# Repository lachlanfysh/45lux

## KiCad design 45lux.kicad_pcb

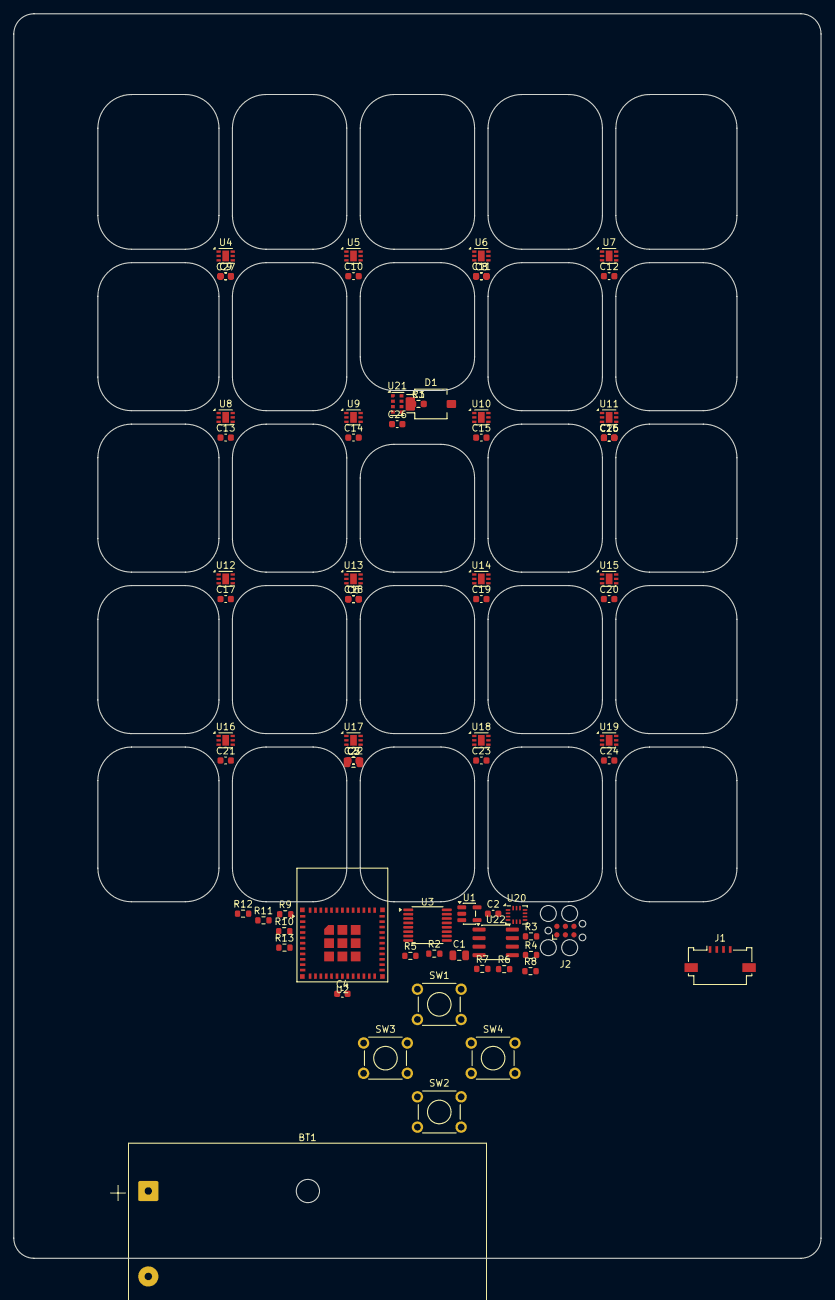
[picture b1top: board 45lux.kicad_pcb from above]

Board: 2 copper layers, 120.0 x 185.0 mm, 70 parts (0 on the bottom side), 23 nets, no tracks yet.

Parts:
BT1: 3xAAA; BatteryHolder_Keystone_2479_3xAAA
C1, C7: 10uF; C_0805_2012Metric
C2, C3, C4, C5, C6, C8, C9, C10, C11, C12, C13, C14, C15, C16, C17, C18, C19, C20, C21, C22, C23, C24, C25, C26, C27: 100nF; C_0603_1608Metric
D1: BPW34-SMD; Osram_BPW34S-SMD
J1: Conn_01x04_Pin; Molex_200528-0040_1x04-1MP_P1.00mm_Horizontal
J2: Conn_02x03_Odd_Even; Tag-Connect_TC2030-IDC-FP_2x03_P1.27mm_Vertical
R1, R2: 4.7K; R_0603_1608Metric
R3, R4, R5, R8, R9, R10, R11, R12, R13: 10K; R_0603_1608Metric
R6: 100K; R_0603_1608Metric
R7: 1M; R_0603_1608Metric
SW1, SW2, SW3, SW4: SW_Push; SW_TH_Tactile_Omron_B3F-106x
U1: AP2112K-3.3; SOT-23-5
U2: ESP32-C6-MINI-1
U3: TCA9546APW; TSSOP-16_4.4x5mm_P0.65mm
U4, U5, U6, U7, U8, U9, U10, U11, U12, U13, U14, U15, U16, U17, U18, U19: OPT3004; DFN-6-1EP_2x2mm_P0.65mm_EP1x1.6mm
U20: LIS2DH; Bosch_LGA-14_3x2.5mm_P0.5mm
U21: AS7343xDLG; AMS_OLGA-8_2x3.1mm_P0.8mm
U22: LM393; SOIC-8_3.9x4.9mm_P1.27mm

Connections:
BTN_DOWN: R11.2, SW2.1
BTN_LEFT: R12.2, SW3.1
BTN_RIGHT: R13.2, SW4.1
BTN_UP: R10.2, SW1.1
ESP_BOOT: J2.6, R4.2
ESP_EN: C4.1, J2.5, R3.2
FLASH_DET: R9.2, U22.1
FLASH_SENSE: D1.2, R6.1, U22.3
FLASH_THRESH: R7.2, R8.1, U22.2
GND: BT1.2, C1.2, C2.2, C3.2, C4.2, C5.2, C6.2, C7.2, C8.2, C9.2, C10.2, C11.2, C12.2, C13.2, C14.2, C15.2, C16.2, C17.2, C18.2, C19.2, C20.2, C21.2, C22.2, C23.2, C24.2, C25.2, C26.2, C27.2, J1.1, J2.4, R6.2, R8.2, SW1.2, SW2.2, SW3.2, SW4.2, U1.2, U3.1, U3.2, U3.8, U3.13, U4.2, U4.3, U5.3, U6.3, U7.3, U8.2, U8.3, U9.3, U10.3, U11.3, U12.2, U12.3, U13.3, U14.3, U15.3, U16.2, U16.3, U17.3, U18.3, U19.3, U20.3, U20.9, U20.10, U20.11, U20.12, U20.13, U20.14, U21.3, U21.5, U22.4, U22.5
I2C_SCL: J1.3, R2.2, U3.14, U20.1, U21.2
I2C_SDA: J1.4, R1.2, U3.15, U20.2, U21.8
MUX_CH0_SCL: U3.5, U4.4, U5.4, U6.4, U7.2, U7.4
MUX_CH0_SDA: U3.4, U4.6, U5.6, U6.2, U6.6, U7.6
MUX_CH1_SCL: U3.7, U8.4, U9.4, U10.4, U11.2, U11.4
MUX_CH1_SDA: U3.6, U8.6, U9.6, U10.2, U10.6, U11.6
MUX_CH2_SCL: U3.10, U12.4, U13.4, U14.4, U15.2, U15.4
MUX_CH2_SDA: U3.9, U12.6, U13.6, U14.2, U14.6, U15.6
MUX_CH3_SCL: U3.12, U16.4, U17.4, U18.4, U19.2, U19.4
MUX_CH3_SDA: U3.11, U16.6, U17.6, U18.2, U18.6, U19.6
unnamed: R5.2, U3.3
VBAT: BT1.1, C1.1, C2.1, U1.1, U1.3
VCC: C3.1, C5.1, C6.1, C7.1, C8.1, C9.1, C10.1, C11.1, C12.1, C13.1, C14.1, C15.1, C16.1, C17.1, C18.1, C19.1, C20.1, C21.1, C22.1, C23.1, C24.1, C25.1, C26.1, C27.1, D1.1, J1.2, J2.1, R1.1, R2.1, R3.1, R4.1, R5.1, R7.1, R9.1, R10.1, R11.1, R12.1, R13.1, U1.5, U3.16, U4.1, U5.1, U5.2, U6.1, U7.1, U8.1, U9.1, U9.2, U10.1, U11.1, U12.1, U13.1, U13.2, U14.1, U15.1, U16.1, U17.1, U17.2, U18.1, U19.1, U20.4, U20.7, U20.8, U21.1, U22.6, U22.8

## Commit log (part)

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2026-06-13 docs: add Codex agent guidance
